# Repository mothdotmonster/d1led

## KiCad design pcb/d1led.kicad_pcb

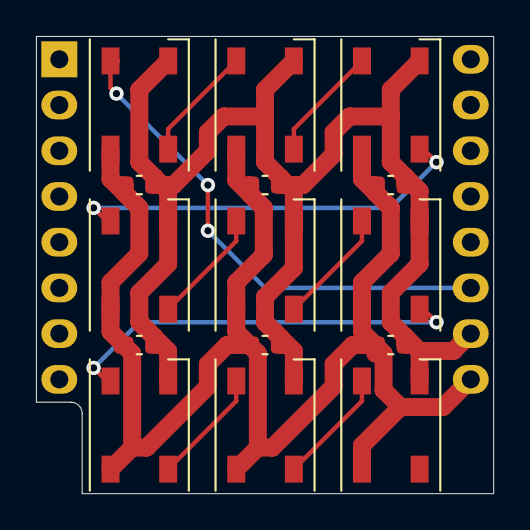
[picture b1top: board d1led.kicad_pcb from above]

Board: 2 copper layers, 25.4 x 25.4 mm, 16 parts (0 on the bottom side), 11 nets.

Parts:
C1, C2, C3, C4, C5, C6: 100nf; C_0603_1608Metric_Pad1.08x0.95mm_HandSolder
D1, D2, D3, D4, D5, D6, D7, D8, D9: WS2812B; LED_WS2812B_PLCC4_5.0x5.0mm_P3.2mm
U1: WeMos_D1_mini; WEMOS_D1_mini_light

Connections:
+5V: C1.1, C2.1, C3.1, C4.1, C5.1, C6.1, D1.1, D2.1, D3.1, D4.1, D5.1, D6.1, D7.1, D8.1, D9.1, U1.9
DIN: D1.4, U1.11
GND: C1.2, C2.2, C3.2, C4.2, C5.2, C6.2, D1.3, D2.3, D3.3, D4.3, D5.3, D6.3, D7.3, D8.3, D9.3, U1.10
unnamed: D1.2, D2.4
unnamed: D2.2, D3.4
unnamed: D3.2, D4.4
unnamed: D4.2, D5.4
unnamed: D5.2, D6.4
unnamed: D6.2, D7.4
unnamed: D7.2, D8.4
unnamed: D8.2, D9.4

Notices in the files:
pcb/d1led.kicad_pcb:
CC-BY-SA
